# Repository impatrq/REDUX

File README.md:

<!-- README.md · Presentación del repo: qué es, hardware, compilar, uf2, cargar y uso. -->

# REDUX firmware

Firmware en C11 del **exoesqueleto de codo REDUX**, sobre Raspberry Pi Pico 2 W (RP2350)
y Pico SDK 2.x. Lee la actividad muscular de **bíceps y tríceps** por EMG, decide la
intención con una **lógica XOR**, y mueve el codo con un motor a través de un puente H
**BTS7960**. Un **encoder magnético AS5600** (I2C) mide el ángulo para respetar los
límites articulares. La seguridad es lo primero: co-contracción, límite alcanzado o falla
del encoder cortan el motor de inmediato.

El plan de desarrollo por fases está en [docs/PLAN.md](docs/PLAN.md); el detalle de
hardware en [docs/hardware.md](docs/hardware.md) y la máquina de estados de seguridad en
[docs/state_machine.md](docs/state_machine.md).

## Estructura del repo

```
src/        Firmware real (app → control / sensors / actuators → hal → SDK)
Pruebas/    Pruebas unitarias (PC) y programas de banco (placa) — ver Pruebas/README.md
tools/      Scripts: make_uf2_wsl.ps1, flash.sh, make_entregas.ps1
docs/       Plan, hardware y máquina de estados
```

## Hardware y pinout

Placa: Raspberry Pi Pico 2 W (RP2350). `src/hal/board.h` y [docs/hardware.md](docs/hardware.md)
son la única fuente de verdad del pinout.

| Señal | GPIO | Notas |
| --- | --- | --- |
| EMG bíceps | GP26 / ADC0 | Señal rectificada (onda completa), sin suavizar, 0–3 V |
| EMG tríceps | GP27 / ADC1 | Ídem |
| BTS7960 RPWM (flexión) | GP8 | PWM 20 kHz, vía 6N137 (no invierte) |
| BTS7960 LPWM (extensión) | GP9 | PWM 20 kHz, vía 6N137 (no invierte) |
| AS5600 SDA / SCL | GP4 / GP5 | I2C0 a 400 kHz, dirección 0x36 |
| LED de estado | GP2 | Solo desarrollo (lo reemplaza la pantalla) |
| Pulsador | GP3 | Solo desarrollo, pull-up interno, activo en bajo |

- **R_EN y L_EN del BTS7960 van fijos a +5 V** del lado del motor: el firmware no los
  maneja. El corte del motor es siempre **RPWM = LPWM = 0**.
- Dos masas aisladas (GND1 potencia / GND2 lógica); el único cruce son RPWM/LPWM por
  optoacopladores 6N137. Con la Pico apagada, los 6N137 dejan ambas señales en alto =
  **freno** (arranque seguro). Detalles en [docs/hardware.md](docs/hardware.md).

## Compilar el firmware

```sh
cmake -B build -G Ninja -DPICO_BOARD=pico2_w
cmake --build build
```

Esto compila el firmware (`redux-firmware`) y los programas de banco (`fase1_check`,
`fase2_check`, `fase3_check`, `emg_check`). Para compilar **solo el firmware**, sin los
bancos:

```sh
cmake -B build -G Ninja -DPICO_BOARD=pico2_w -DREDUX_BUILD_BANCOS=OFF
cmake --build build
```

### Generar el `.uf2` (picotool bloqueado por Device Guard)

En esta máquina, Device Guard / Smart App Control a veces bloquea `picotool.exe`, el paso
de empaquetado que CMake invoca al final: el `.elf` se enlaza bien (`build/redux-firmware.elf`),
pero el build corta sin producir el `.uf2`. Para generarlo se usa un `picotool` nativo de
Linux compilado en WSL 2:

```powershell
tools\make_uf2_wsl.ps1
```

La primera vez compila `picotool` dentro de WSL (en `~/.local/bin`, no en el repo), usando
como `PICO_SDK_PATH` el SDK ya instalado en Windows; después solo convierte. Para otro
ejecutable (por ejemplo un banco):

```powershell
tools\make_uf2_wsl.ps1 -Elf build\emg_check.elf -Uf2 build\emg_check.uf2
```

## Cargar en la Pico

Poner la Pico en modo BOOTSEL (mantener el botón al conectar) y copiar el `.uf2` a la
unidad `RPI-RP2`, o bien:

```sh
tools/flash.sh
```

## Pruebas

- **Unitarias (PC, Unity):** la forma oficial es por WSL —
  `powershell -ExecutionPolicy Bypass -File Pruebas\unitarias\run_tests_wsl.ps1`.
- **De banco (sobre la placa):** un programa por fase en `Pruebas/banco/`.

Todo el detalle en [Pruebas/README.md](Pruebas/README.md).

## Comandos serie del firmware

Por el monitor serie USB (una línea por comando):

| Comando | Efecto |
| --- | --- |
| `b N` | Intensidad simulada de bíceps (flexión) al N % (0–100) |
| `t N` | Intensidad simulada de tríceps (extensión) al N % |
| `r` | Reposo: ambos canales a 0 |
| `ok` | Confirmar (arranque / calibración) |
| `cancel` | Cancelar el paso actual |
| `recal` | Volver a calibrar desde el rango (ROM) |
| `hang` | Solo en modo banco: cuelga el lazo para probar el watchdog |

En el banco (sin electrodos) la fuente de EMG es **simulada por serie** (`b`/`t`/`r`); con
el paciente conectado se pasa a ADC (ver `EMG_SOURCE` en `src/common/config.h`). El
firmware emite un reporte de estado por USB periódicamente.

## Estados (supervisor de seguridad)

```
BOOT → CHECK_ENC → CALIB_ROM → CALIB_REST → CALIB_MVC → ARMING → RUN
                                                                    ↕
                                                                  FAULT
```

El motor **solo recibe PWM en `RUN`**. Cualquier falla (encoder, saturación de EMG,
sobrepaso del ciclo) lleva a `FAULT` con corte inmediato; el rearme exige lecturas
estables y ambos músculos en reposo. Transiciones completas en
[docs/state_machine.md](docs/state_machine.md).

## Abrir el proyecto en VS Code

La carpeta `.vscode/` **no se versiona** (es configuración local de cada máquina), así que
al clonar el repo no viene incluida. Dos formas de trabajar:

- **Extensión Raspberry Pi Pico:** instalar la extensión *Raspberry Pi Pico* en VS Code y
  usar *Pico: Import Project* sobre la carpeta del repo (board `pico2_w`, Pico SDK 2.x). La
  extensión regenera su propia configuración de `.vscode/` y los comandos de build/flash.
- **Por línea de comandos:** no hace falta VS Code. Alcanza con tener instalados el Pico
  SDK 2.x, CMake y Ninja, y usar los comandos de *Compilar el firmware* de arriba.

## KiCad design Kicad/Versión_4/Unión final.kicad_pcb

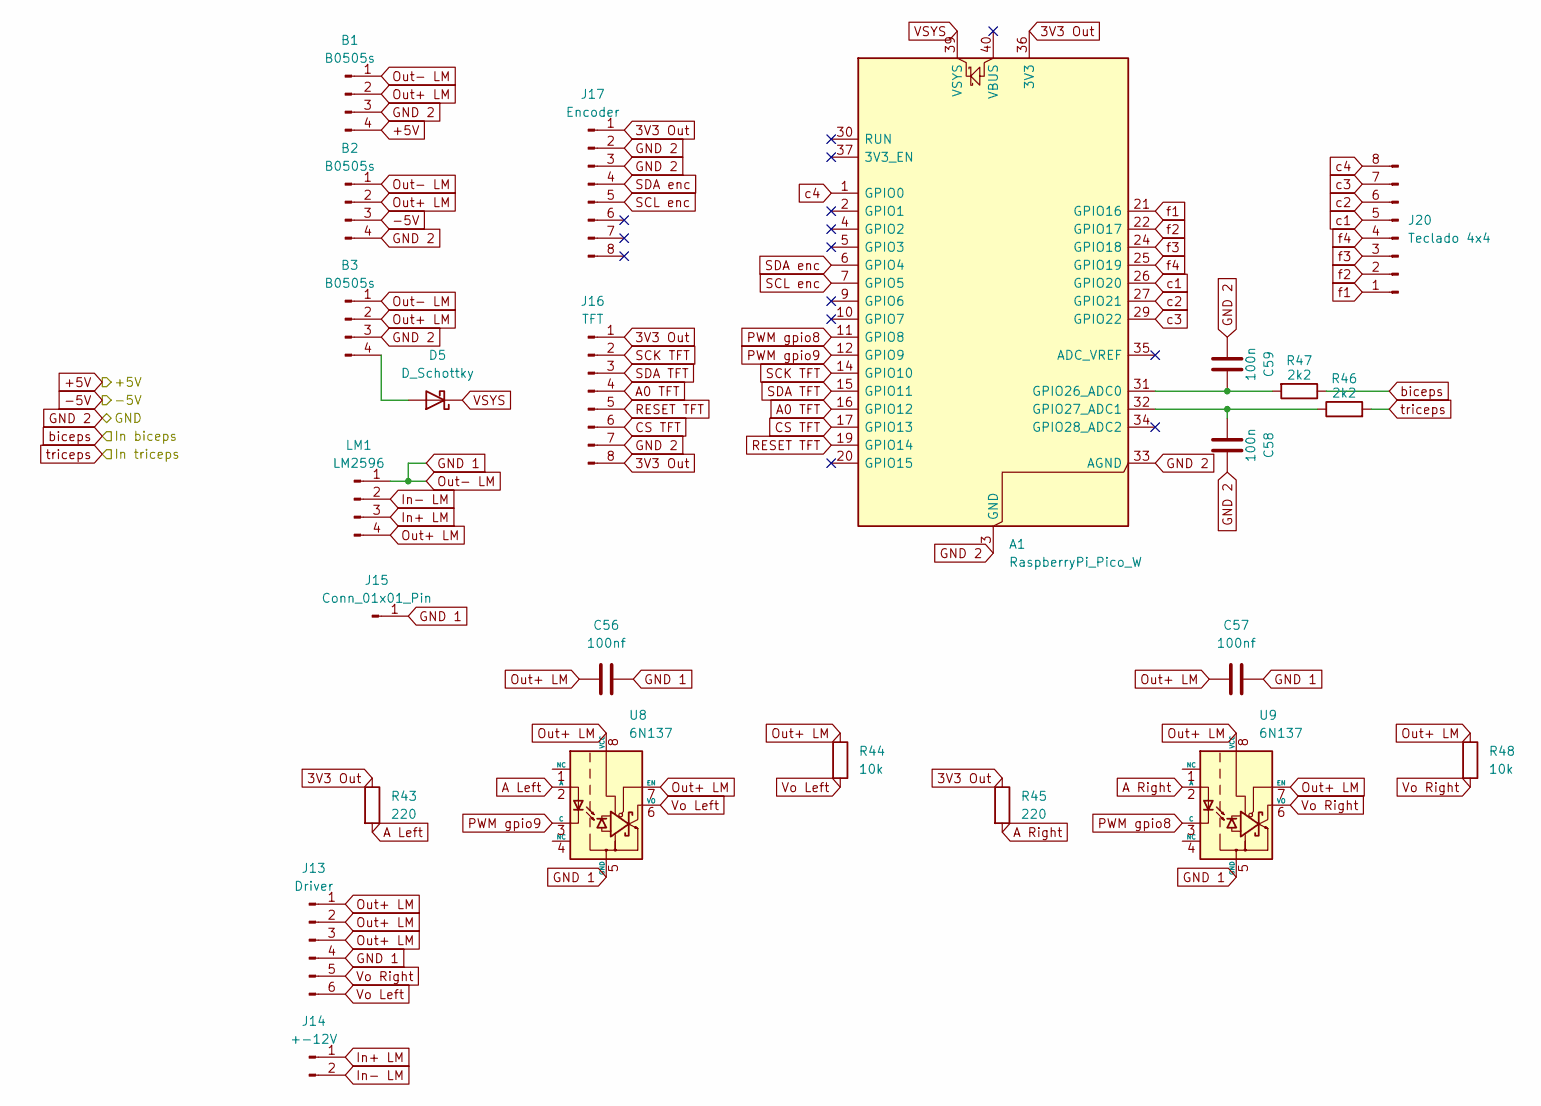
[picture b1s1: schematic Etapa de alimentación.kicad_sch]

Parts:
A1: RaspberryPi_Pico_W; RaspberryPi_Pico_Common_THT
B1, B2, B3: B0505s; B0505S-1w
C56, C57: 100nf; C_Disc_D10.0mm_W2.5mm_P5.00mm
C58, C59: 100n; C_0805_2012Metric_Pad1.18x1.45mm_HandSolder
D5: D_Schottky; D_DO-41_SOD81_P10.16mm_Horizontal
J13: Driver; PinHeader_1x06_P2.54mm_Vertical
J14: +-12V; TerminalBlock_MetzConnect_Type011_RT05502HBLC_1x02_P5.00mm_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
J15: Conn_01x01_Pin; PinHeader_1x01_P2.54mm_Vertical
J16: TFT; PinHeader_1x08_P2.54mm_Vertical
J17: Encoder; Molex_KK-254_AE-6410-08A_1x08_P2.54mm_Vertical
J20: Teclado 4x4; PinHeader_1x08_P2.54mm_Vertical
LM1: LM2596
R43, R45: 220; R_Axial_DIN0207_L6.3mm_D2.5mm_P10.16mm_Horizontal
R44, R48: 10k; R_Axial_DIN0207_L6.3mm_D2.5mm_P10.16mm_Horizontal
R46, R47: 2k2; R_Axial_DIN0207_L6.3mm_D2.5mm_P10.16mm_Horizontal
U8, U9: 6N137; DIP-8_W7.62mm

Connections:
3V3 Out: A1.36 (3V3), J16.1, J16.8, J17.1, R43.1, R45.1
+5V: B1.4; also elsewhere on the board
-5V: B2.3; also elsewhere on the board
A0 TFT: A1.16 (GPIO12), J16.4
A Left: R43.2, U8.2 (A)
A Right: R45.2, U9.2 (A)
CS TFT: A1.17 (GPIO13), J16.6
GND: A1.3 (GND), A1.8 (GND), A1.13 (GND), A1.18 (GND), A1.23 (GND), A1.28 (GND), A1.33 (AGND), A1.38 (GND), B1.3, B2.4, B3.3, C58.2, C59.1, J16.7, J17.2, J17.3; also elsewhere on the board
GND 1: B1.1, B2.1, B3.1, C56.2, C57.2, J13.4, J15.1 (Pin_1_1), LM1.1, U8.5 (GND), U9.5 (GND)
In+ LM: J14.1, LM1.3
In- LM: J14.2, LM1.2
unnamed: A1.31 (GPIO26_ADC0), C59.2, R47.2
unnamed: A1.32 (GPIO27_ADC1), C58.1, R46.1
unnamed: B3.4, D5.2 (A)
Out+ LM: B1.2, B2.2, B3.2, C56.1, C57.1, J13.1, J13.2, J13.3, LM1.4, R44.1, R48.1, U8.7 (EN), U8.8 (VCC), U9.7 (EN), U9.8 (VCC)
PWM gpio8: A1.11 (GPIO8), U9.3 (C)
PWM gpio9: A1.12 (GPIO9), U8.3 (C)
RESET TFT: A1.19 (GPIO14), J16.5
Rectificador biceps: R47.1; also elsewhere on the board
Rectificador triceps: R46.2; also elsewhere on the board
SCK TFT: A1.14 (GPIO10), J16.2
SCL enc: A1.7 (GPIO5), J17.5
SDA TFT: A1.15 (GPIO11), J16.3
SDA enc: A1.6 (GPIO4), J17.4
VSYS: A1.39 (VSYS), D5.1 (K)
Vo Left: J13.6, R44.2, U8.6 (VO)
Vo Right: J13.5, R48.2, U9.6 (VO)
c1: A1.26 (GPIO20), J20.5
c2: A1.27 (GPIO21), J20.6
c3: A1.29 (GPIO22), J20.7
c4: A1.1 (GPIO0), J20.8
f1: A1.21 (GPIO16), J20.1
f2: A1.22 (GPIO17), J20.2
f3: A1.24 (GPIO18), J20.3
f4: A1.25 (GPIO19), J20.4

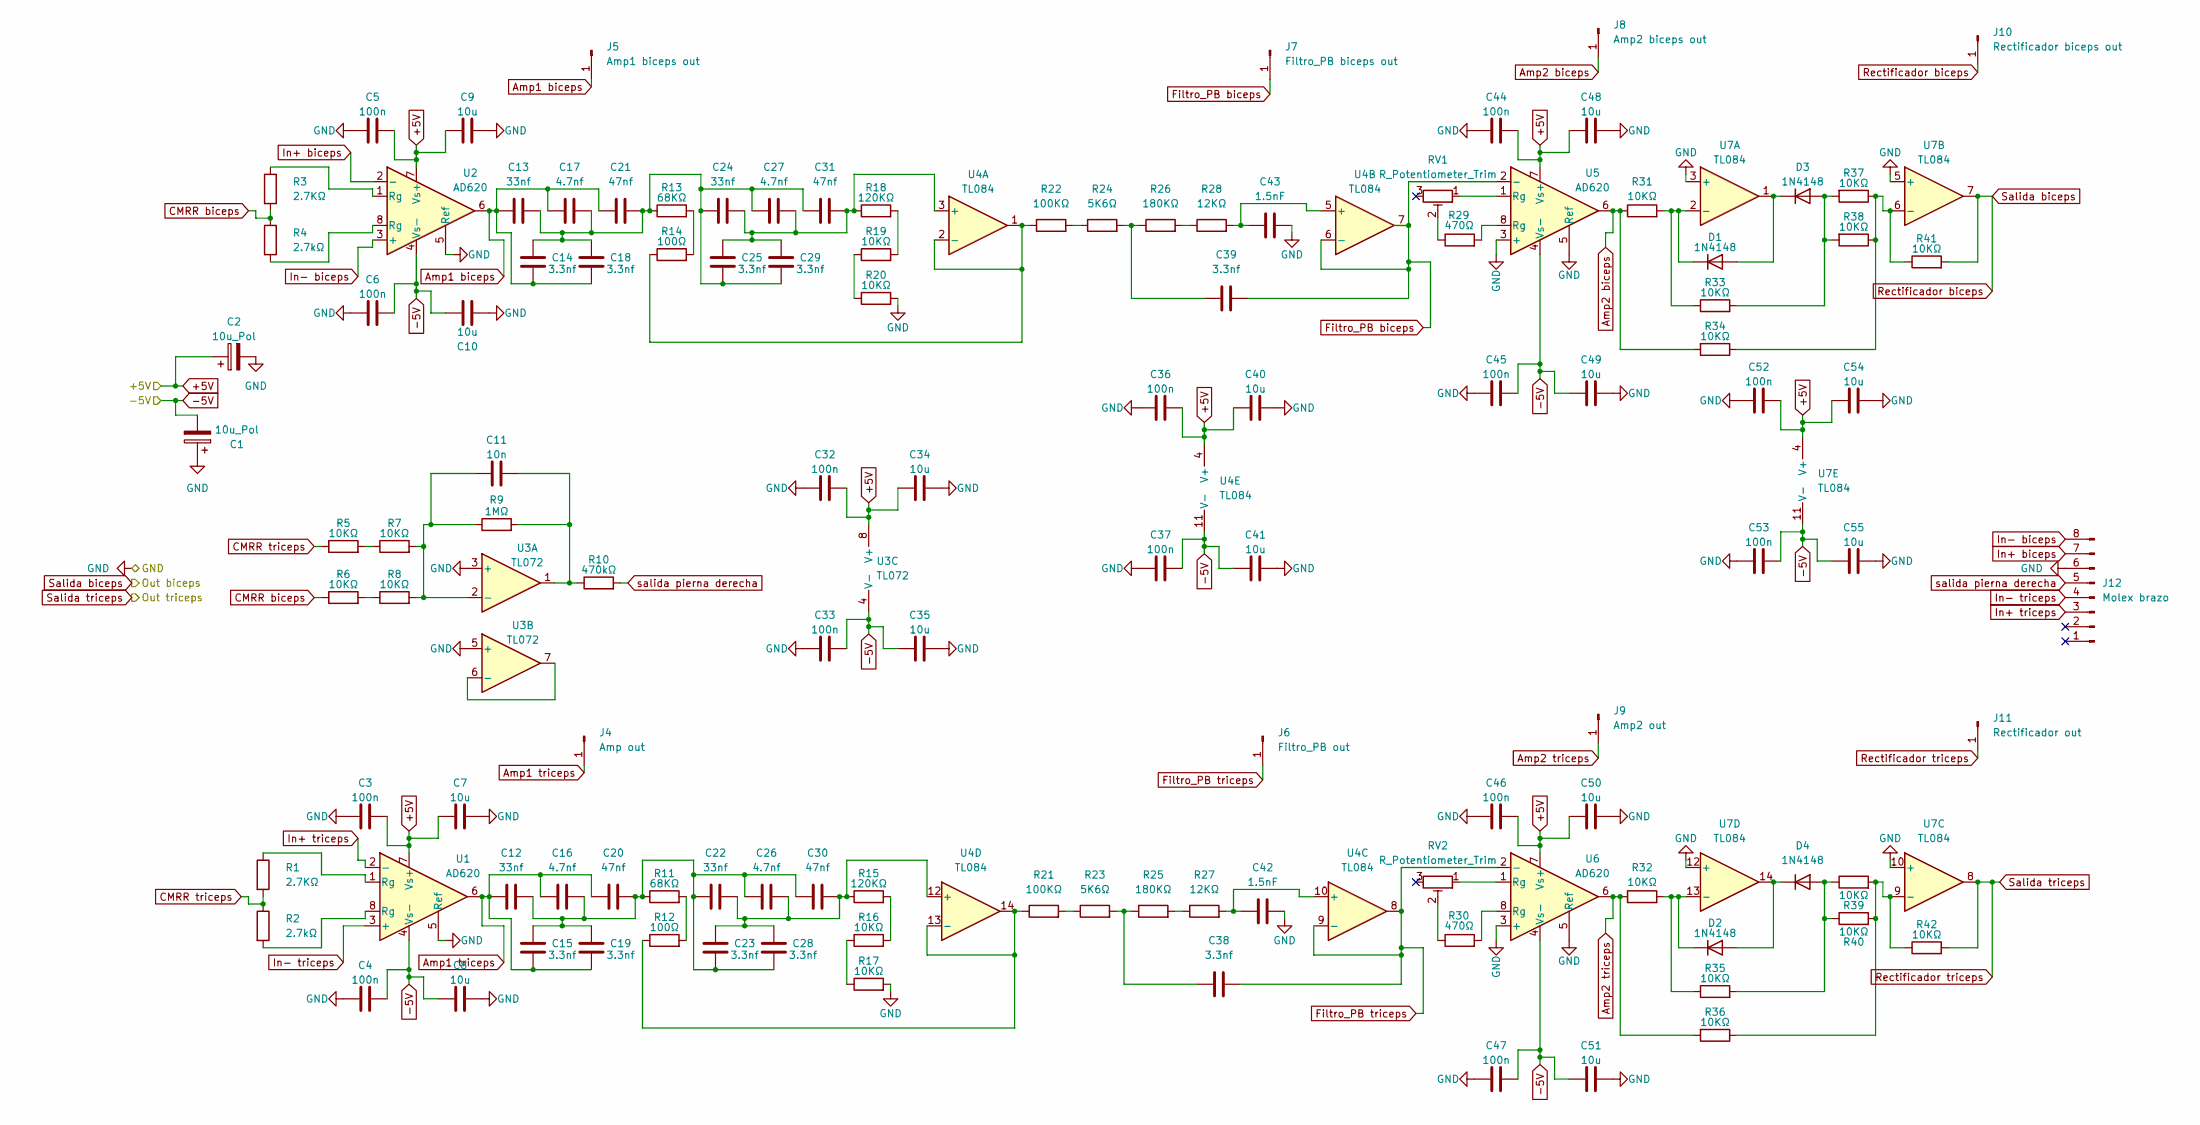
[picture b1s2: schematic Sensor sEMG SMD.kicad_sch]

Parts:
C1, C2: 10u_Pol; CP_Radial_D5.0mm_P2.00mm
C3, C4, C5, C6, C32, C33, C36, C37, C44, C45, C46, C47, C52, C53: 100n; C_0805_2012Metric_Pad1.18x1.45mm_HandSolder
C7, C8, C9, C10, C34, C35, C40, C41, C48, C49, C50, C51, C54, C55: 10u; C_0805_2012Metric_Pad1.18x1.45mm_HandSolder
C11: 10n; C_0805_2012Metric_Pad1.18x1.45mm_HandSolder
C12, C13, C22, C24: 33nf; C_0805_2012Metric_Pad1.18x1.45mm_HandSolder
C14, C15, C18, C19, C23, C25, C28, C29, C38, C39: 3.3nf; C_0805_2012Metric_Pad1.18x1.45mm_HandSolder
C16, C17, C26, C27: 4.7nf; C_0805_2012Metric_Pad1.18x1.45mm_HandSolder
C20, C21, C30, C31: 47nf; C_0805_2012Metric_Pad1.18x1.45mm_HandSolder
C42, C43: 1.5nF; C_0805_2012Metric_Pad1.18x1.45mm_HandSolder
D1, D2, D3, D4: 1N4148; D_SOD-123
J4: Amp out; PinHeader_1x01_P2.00mm_Vertical
J5: Amp1 biceps out; PinHeader_1x01_P2.00mm_Vertical
J6: Filtro_PB out; PinHeader_1x01_P2.00mm_Vertical
J7: Filtro_PB biceps out; PinHeader_1x01_P2.00mm_Vertical
J8: Amp2 biceps out; PinHeader_1x01_P2.00mm_Vertical
J9: Amp2 out; PinHeader_1x01_P2.00mm_Vertical
J10: Rectificador biceps out; PinHeader_1x01_P2.00mm_Vertical
J11: Rectificador out; PinHeader_1x01_P2.00mm_Vertical
J12: Molex brazo; Molex_KK-254_AE-6410-08A_1x08_P2.54mm_Vertical
R1, R3: 2.7KΩ; R_0805_2012Metric_Pad1.20x1.40mm_HandSolder
R2, R4: 2.7kΩ; R_0805_2012Metric_Pad1.20x1.40mm_HandSolder
R5, R6, R7, R8, R16, R17, R19, R20, R31, R32, R33, R34, R35, R36, R37, R38, R39, R40, R41, R42: 10KΩ; R_0805_2012Metric_Pad1.20x1.40mm_HandSolder
R9: 1MΩ; R_0805_2012Metric_Pad1.20x1.40mm_HandSolder
R10: 470kΩ; R_0805_2012Metric_Pad1.20x1.40mm_HandSolder
R11, R13: 68KΩ; R_0805_2012Metric_Pad1.20x1.40mm_HandSolder
R12, R14: 100Ω; R_0805_2012Metric_Pad1.20x1.40mm_HandSolder
R15, R18: 120KΩ; R_0805_2012Metric_Pad1.20x1.40mm_HandSolder
R21, R22: 100KΩ; R_0805_2012Metric_Pad1.20x1.40mm_HandSolder
R23, R24: 5K6Ω; R_0805_2012Metric_Pad1.20x1.40mm_HandSolder
R25, R26: 180KΩ; R_0805_2012Metric_Pad1.20x1.40mm_HandSolder
R27, R28: 12KΩ; R_0805_2012Metric_Pad1.20x1.40mm_HandSolder
R29, R30: 470Ω; R_0805_2012Metric_Pad1.20x1.40mm_HandSolder
RV1, RV2: R_Potentiometer_Trim; Potentiometer_Bourns_3296W_Vertical
U1, U2, U5, U6: AD620; SOIC-8_3.9x4.9mm_P1.27mm
U3: TL072; SOIC-8_3.9x4.9mm_P1.27mm
U4, U7: TL084; SOIC-14_3.9x8.7mm_P1.27mm

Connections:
+5V: C2.1, C3.2, C5.2, C7.1, C9.1, C32.2, C34.1, C36.2, C40.1, C44.2, C46.2, C48.1, C50.1, C52.2, C54.1, U1.7 (Vs+), U2.7 (Vs+), U3.8 (V+), U4.4 (V+), U5.7 (Vs+), U6.7 (Vs+), U7.4 (V+); also elsewhere on the board
-5V: C1.2, C4.2, C6.2, C8.1, C10.2, C33.2, C35.1, C37.2, C41.1, C45.2, C47.2, C49.1, C51.1, C53.2, C55.1, U1.4 (Vs-), U2.4 (Vs-), U3.4 (V-), U4.11 (V-), U5.4 (Vs-), U6.4 (Vs-), U7.11 (V-); also elsewhere on the board
Amp1 biceps: C13.1, C14.2, C17.1, C18.2, C21.1, J5.1 (Pin_1_1), U2.6
Amp1 triceps: C12.1, C15.2, C16.1, C19.2, C20.1, J4.1 (Pin_1_1), U1.6
Amp2 biceps: J8.1 (Pin_1_1), R31.1, R34.2, U5.6
Amp2 triceps: J9.1 (Pin_1_1), R32.1, R36.2, U6.6
CMRR biceps: R3.2, R4.1, R6.1
CMRR triceps: R1.2, R2.1, R5.1
Filtro_PB biceps: C39.2, J7.1 (Pin_1_1), U4.6 (-), U4.7, U5.2 (-)
Filtro_PB triceps: C38.2, J6.1 (Pin_1_1), U4.8, U4.9 (-), U6.2 (-)
GND: C1.1, C2.2, C3.1, C4.1, C5.1, C6.1, C7.2, C8.2, C9.2, C10.1, C32.1, C33.1, C34.2, C35.2, C36.1, C37.1, C40.2, C41.2, C42.2, C43.2, C44.1, C45.1, C46.1, C47.1, C48.2, C49.2, C50.2, C51.2, C52.1, C53.1, C54.2, C55.2, J12.6, R17.2, R20.2, U1.5 (Ref), U2.5 (Ref), U3.3 (+), U3.5 (+), U5.3 (+), U5.5 (Ref), U6.3 (+), U6.5 (Ref), U7.3 (+), U7.5 (+), U7.10 (+), U7.12 (+); also elsewhere on the board
In+ biceps: J12.7, U2.2 (-)
In+ triceps: J12.3, U1.2 (-)
In- biceps: J12.8, U2.3 (+)
In- triceps: J12.4, U1.3 (+)
unnamed: C11.2, R9.2, R10.1, U3.1
unnamed: C12.2, C15.1, C16.2, C19.1, C20.2, C22.1, C23.2, C26.1, C28.2, C30.1, R11.1
unnamed: C13.2, C14.1, C17.2, C18.1, C21.2, C24.1, C25.2, C27.1, C29.2, C31.1, R13.1
unnamed: C38.1, R23.2, R25.1
unnamed: C39.1, R24.2, R26.1
unnamed: D1.2 (A), D3.1 (K), U7.1
unnamed: D1.1 (K), R31.2, R33.1, U7.2 (-)
unnamed: D2.2 (A), D4.1 (K), U7.14
unnamed: D2.1 (K), R32.2, R35.1, U7.13 (-)
unnamed: D3.2 (A), R33.2, R37.2, R38.2
unnamed: D4.2 (A), R35.2, R39.1, R40.1
unnamed: R1.1, U1.1 (Rg)
unnamed: R2.2, U1.8 (Rg)
unnamed: R3.1, U2.1 (Rg)
unnamed: R4.2, U2.8 (Rg)
unnamed: R5.2, R7.1
unnamed: R6.2, R8.1
unnamed: R11.2, R12.2
unnamed: R13.2, R14.2
unnamed: R15.2, R16.2
unnamed: R16.1, R17.1
unnamed: R18.2, R19.2
unnamed: R19.1, R20.1
unnamed: R21.2, R23.1
unnamed: R22.2, R24.1
unnamed: R25.2, R27.1
unnamed: R26.2, R28.1
unnamed: R29.1, RV1.2
unnamed: R29.2, U5.8 (Rg)
unnamed: R30.1, RV2.2
unnamed: R30.2, U6.8 (Rg)
unnamed: RV1.1, U5.1 (Rg)
unnamed: RV2.1, U6.1 (Rg)
unnamed: C11.1, R7.2, R8.2, R9.1, U3.2 (-)
unnamed: U3.6 (-), U3.7
unnamed: C24.2, C25.1, C27.2, C29.1, C31.2, R18.1, U4.3 (+)
unnamed: R14.1, R22.1, U4.1, U4.2 (-)
unnamed: C43.1, R28.2, U4.5 (+)
unnamed: C42.1, R27.2, U4.10 (+)
unnamed: C22.2, C23.1, C26.2, C28.1, C30.2, R15.1, U4.12 (+)
unnamed: R12.1, R21.1, U4.13 (-), U4.14
unnamed: R34.1, R37.1, R38.1, R41.1, U7.6 (-)
unnamed: R36.1, R39.2, R40.2, R42.1, U7.9 (-)
Rectificador biceps: J10.1 (Pin_1_1), R41.2, U7.7; also elsewhere on the board
Rectificador triceps: J11.1 (Pin_1_1), R42.2, U7.8; also elsewhere on the board
salida pierna derecha: J12.5, R10.2

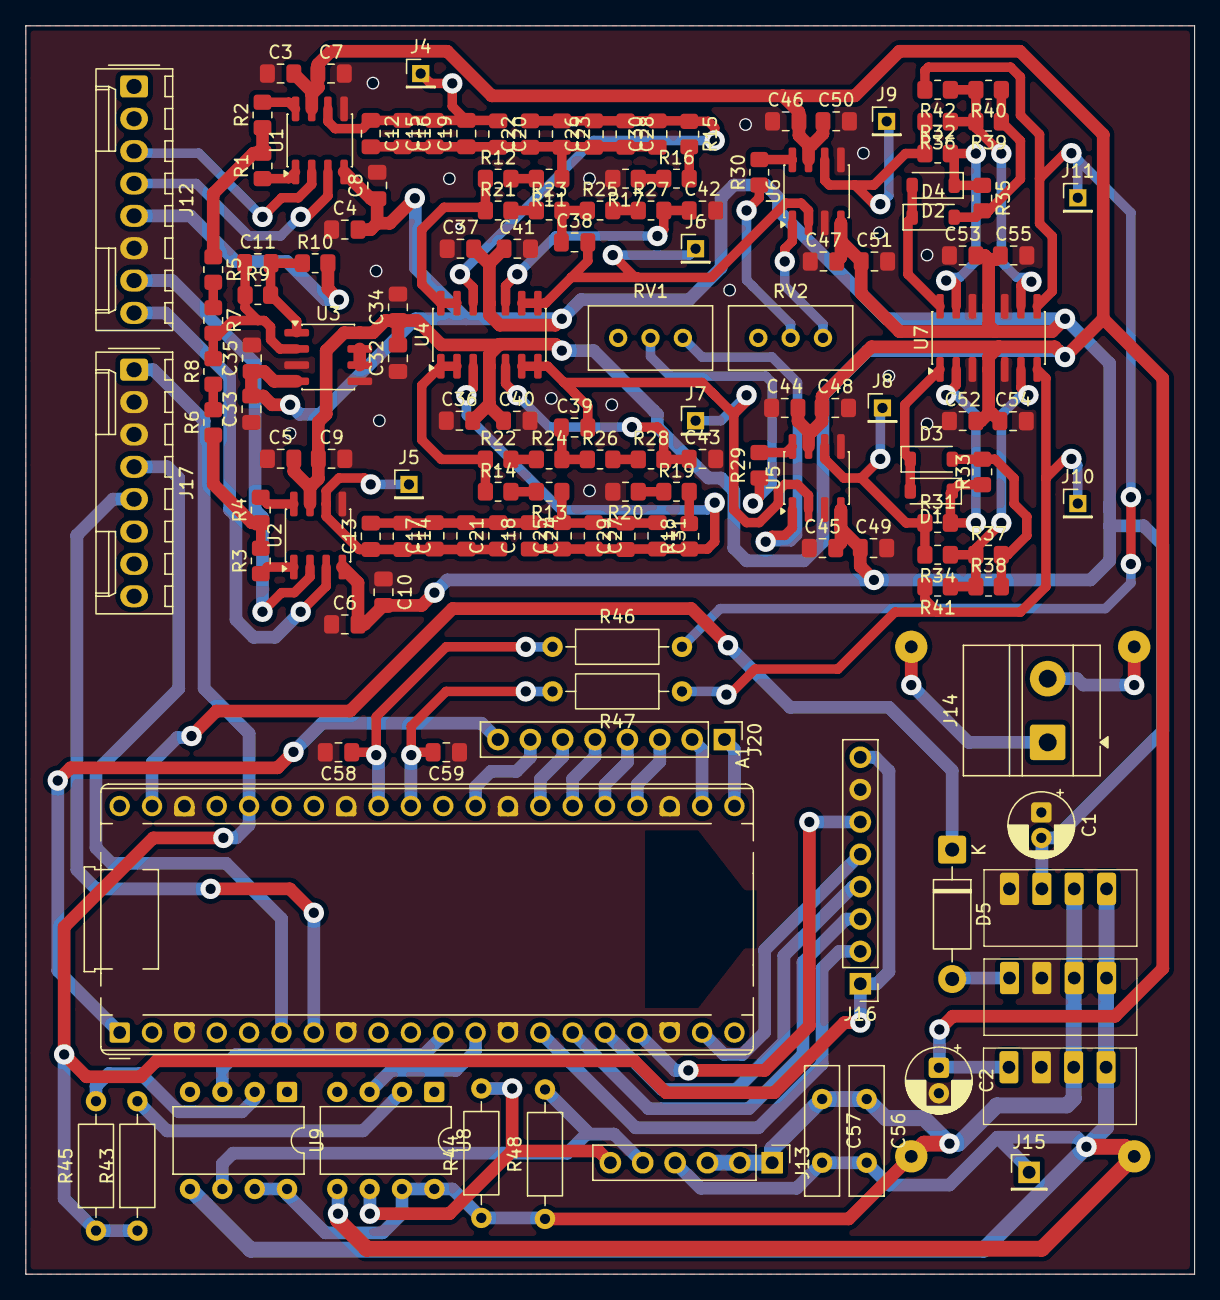
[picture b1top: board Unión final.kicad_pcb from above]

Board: 2 copper layers, 91.8 x 98.0 mm, 143 parts (1 on the bottom side), 91 nets.

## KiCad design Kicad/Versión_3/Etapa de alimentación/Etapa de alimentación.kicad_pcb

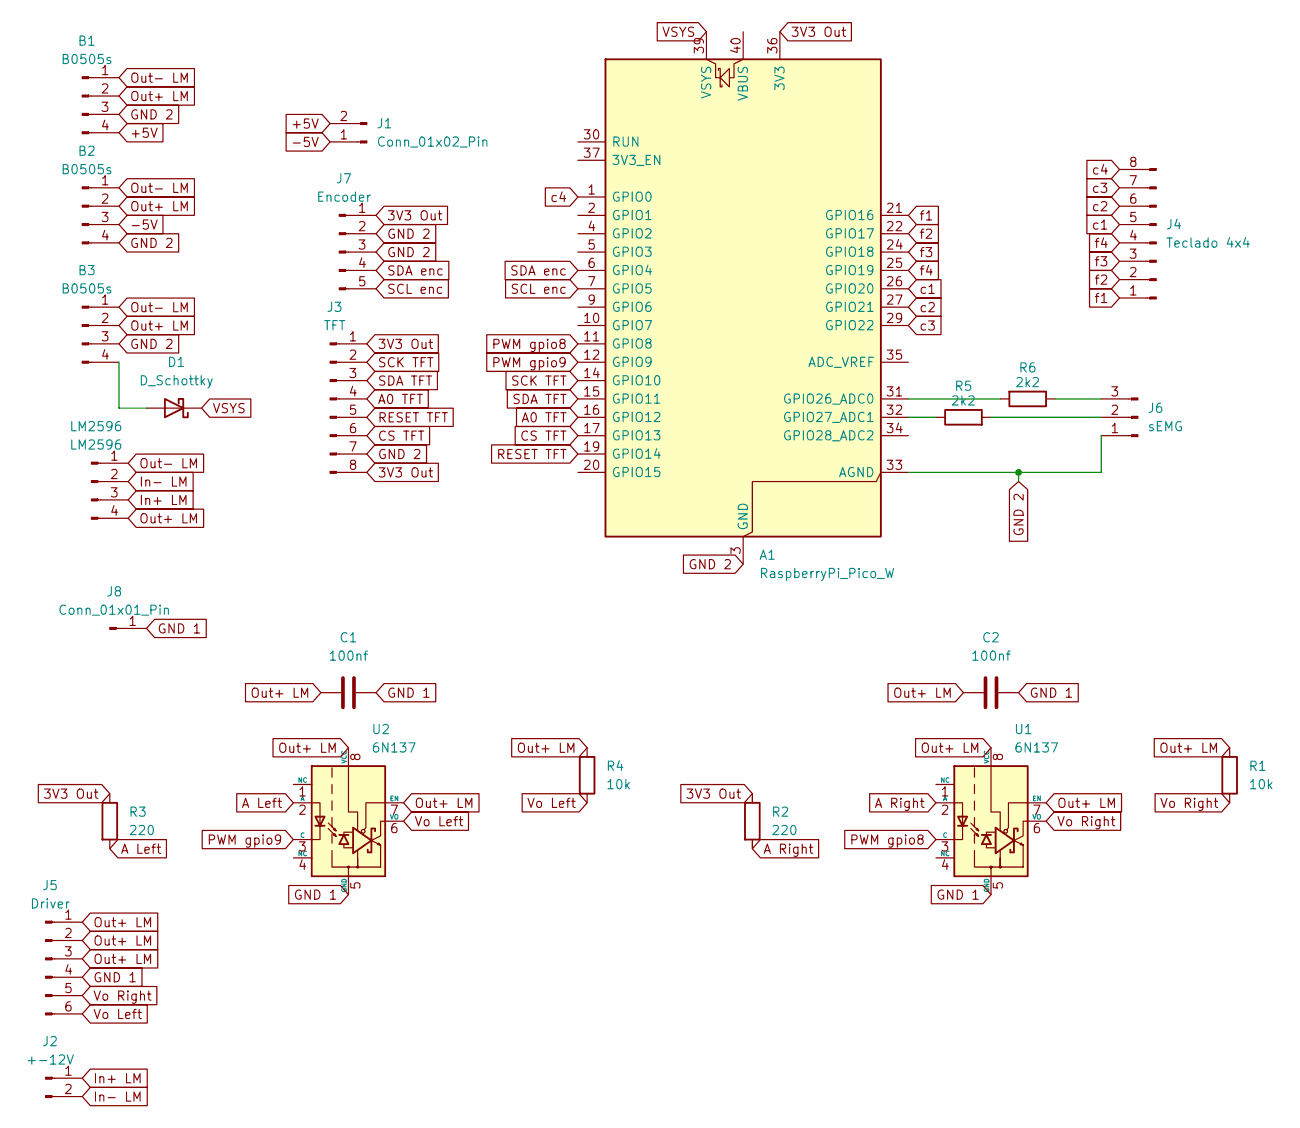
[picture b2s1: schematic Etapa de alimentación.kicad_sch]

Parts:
A1: RaspberryPi_Pico_W; RaspberryPi_Pico_Common_THT
B1, B2, B3: B0505s; B0505S-1w
C1, C2: 100nf; C_Disc_D10.0mm_W2.5mm_P5.00mm
D1: D_Schottky; D_5W_P12.70mm_Horizontal
J1: Conn_01x02_Pin; TerminalBlock_MetzConnect_Type011_RT05502HBLC_1x02_P5.00mm_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
J2: +-12V; TerminalBlock_MetzConnect_Type011_RT05502HBLC_1x02_P5.00mm_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
J3: TFT; PinHeader_1x08_P2.54mm_Vertical
J4: Teclado 4x4; PinHeader_1x08_P2.54mm_Vertical
J5: Driver; PinHeader_1x06_P2.54mm_Vertical
J6: sEMG; TerminalBlock_MetzConnect_Type011_RT05503HBLC_1x03_P5.00mm_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
J7: Encoder; TerminalBlock_MetzConnect_Type011_RT05505HBLC_1x05_P5.00mm_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
J8: Conn_01x01_Pin; PinHeader_1x01_P2.54mm_Vertical
LM2596: LM2596
R1, R4: 10k; R_Axial_DIN0207_L6.3mm_D2.5mm_P10.16mm_Horizontal
R2, R3: 220; R_Axial_DIN0207_L6.3mm_D2.5mm_P10.16mm_Horizontal
R5, R6: 2k2; R_Axial_DIN0207_L6.3mm_D2.5mm_P10.16mm_Horizontal
U1, U2: 6N137; DIP-8_W7.62mm

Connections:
3V3 Out: A1.36 (3V3), J3.1, J3.8, J7.1, R2.1, R3.1
+5V: B1.4, J1.2
-5V: B2.3, J1.1
A0 TFT: A1.16 (GPIO12), J3.4
A Left: R3.2, U2.2 (A)
A Right: R2.2, U1.2 (A)
CS TFT: A1.17 (GPIO13), J3.6
GND 1: C1.2, C2.2, J5.4, J8.1 (Pin_1_1), U1.5 (GND), U2.5 (GND)
GND 2: A1.3 (GND), A1.8 (GND), A1.13 (GND), A1.18 (GND), A1.23 (GND), A1.28 (GND), A1.33 (AGND), A1.38 (GND), B1.3, B2.4, B3.3, J3.7, J6.1, J7.2, J7.3
In+ LM: J2.1, LM2596.3
In- LM: J2.2, LM2596.2
unnamed: A1.31 (GPIO26_ADC0), R6.2
unnamed: A1.32 (GPIO27_ADC1), R5.1
unnamed: B3.4, D1.2 (A)
unnamed: J6.2, R5.2
unnamed: J6.3, R6.1
Out+ LM: B1.2, B2.2, B3.2, C1.1, C2.1, J5.1, J5.2, J5.3, LM2596.4, R1.1, R4.1, U1.7 (EN), U1.8 (VCC), U2.7 (EN), U2.8 (VCC)
Out- LM: B1.1, B2.1, B3.1, LM2596.1
PWM gpio8: A1.11 (GPIO8), U1.3 (C)
PWM gpio9: A1.12 (GPIO9), U2.3 (C)
RESET TFT: A1.19 (GPIO14), J3.5
SCK TFT: A1.14 (GPIO10), J3.2
SCL enc: A1.7 (GPIO5), J7.5
SDA TFT: A1.15 (GPIO11), J3.3
SDA enc: A1.6 (GPIO4), J7.4
VSYS: A1.39 (VSYS), D1.1 (K)
Vo Left: J5.6, R4.2, U2.6 (VO)
Vo Right: J5.5, R1.2, U1.6 (VO)
c1: A1.26 (GPIO20), J4.5
c2: A1.27 (GPIO21), J4.6
c3: A1.29 (GPIO22), J4.7
c4: A1.1 (GPIO0), J4.8
f1: A1.21 (GPIO16), J4.1
f2: A1.22 (GPIO17), J4.2
f3: A1.24 (GPIO18), J4.3
f4: A1.25 (GPIO19), J4.4

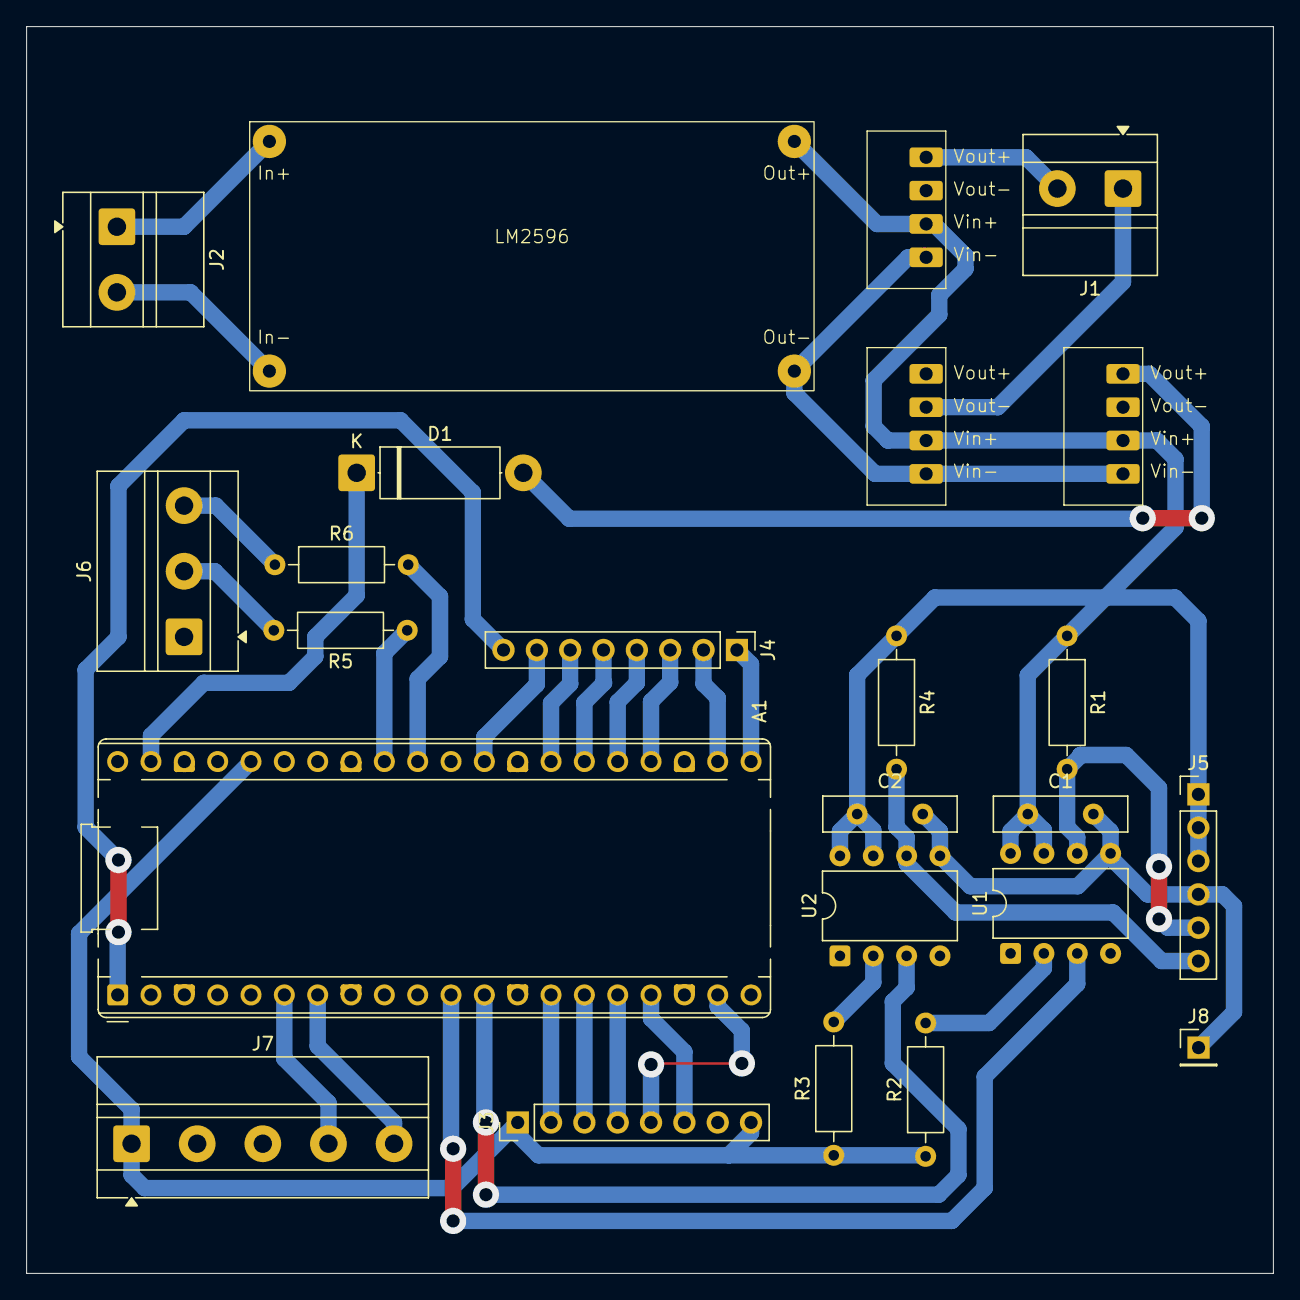
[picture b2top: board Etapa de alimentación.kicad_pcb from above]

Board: 2 copper layers, 95.0 x 95.0 mm, 24 parts (0 on the bottom side), 36 nets.

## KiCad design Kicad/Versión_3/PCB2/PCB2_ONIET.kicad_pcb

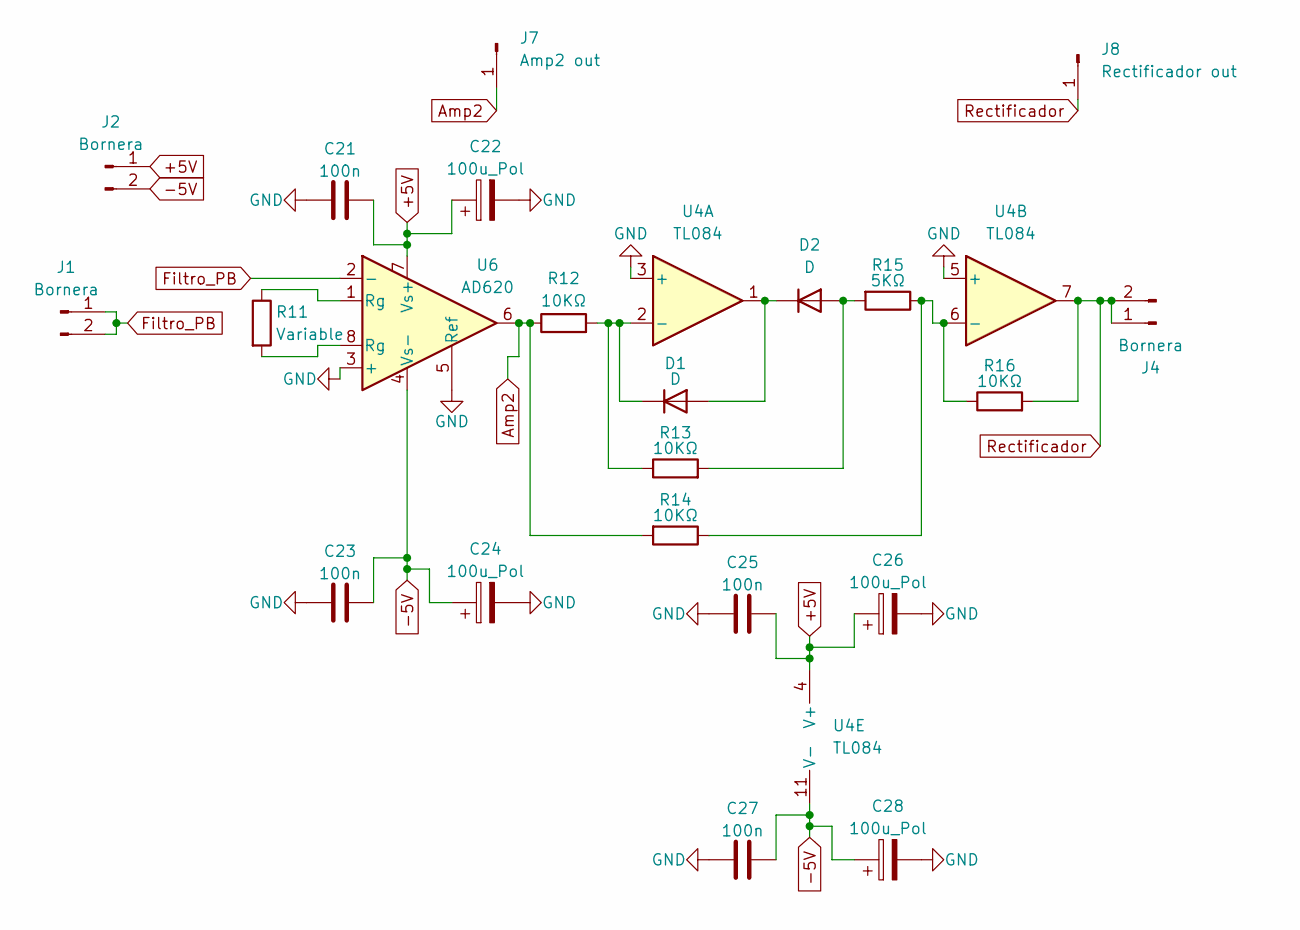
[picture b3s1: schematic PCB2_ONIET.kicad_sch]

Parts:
C21, C23, C25, C27: 100n; C_Disc_D10.5mm_W5.0mm_P10.00mm
C22, C24, C26, C28: 100u_Pol; C_Radial_D5.0mm_H11.0mm_P2.00mm
D1, D2: D; D_5W_P12.70mm_Horizontal
J1, J2, J4: Bornera; TerminalBlock_MetzConnect_Type011_RT05502HBLC_1x02_P5.00mm_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
J7: Amp2 out; PinHeader_1x01_P2.00mm_Vertical
J8: Rectificador out; PinHeader_1x01_P2.00mm_Vertical
R11: Variable; R_Axial_DIN0207_L6.3mm_D2.5mm_P10.16mm_Horizontal
R12, R13, R14, R16: 10KΩ; R_Axial_DIN0207_L6.3mm_D2.5mm_P10.16mm_Horizontal
R15: 5KΩ; R_Axial_DIN0207_L6.3mm_D2.5mm_P10.16mm_Horizontal
U4: TL084; DIP-14_W7.62mm_LongPads
U6: AD620; DIP-8_W7.62mm

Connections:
+5V: C21.2, C22.1, C25.2, C26.1, J2.1, U4.4 (V+), U6.7 (Vs+)
-5V: C23.2, C24.1, C27.2, C28.1, J2.2, U4.11 (V-), U6.4 (Vs-)
Amp2: J7.1 (Pin_1_1), R12.1, R14.2, U6.6
Filtro_PB: J1.1, J1.2, U6.2 (-)
GND: C21.1, C22.2, C23.1, C24.2, C25.1, C26.2, C27.1, C28.2, U4.3 (+), U4.5 (+), U6.3 (+), U6.5 (Ref)
unnamed: D1.2 (A), D2.1 (K), U4.1
unnamed: D1.1 (K), R12.2, R13.1, U4.2 (-)
unnamed: D2.2 (A), R13.2, R15.2
unnamed: R11.1, U6.1 (Rg)
unnamed: R11.2, U6.8 (Rg)
unnamed: R14.1, R15.1, R16.1, U4.6 (-)
Rectificador: J4.1, J4.2, J8.1 (Pin_1_1), R16.2, U4.7

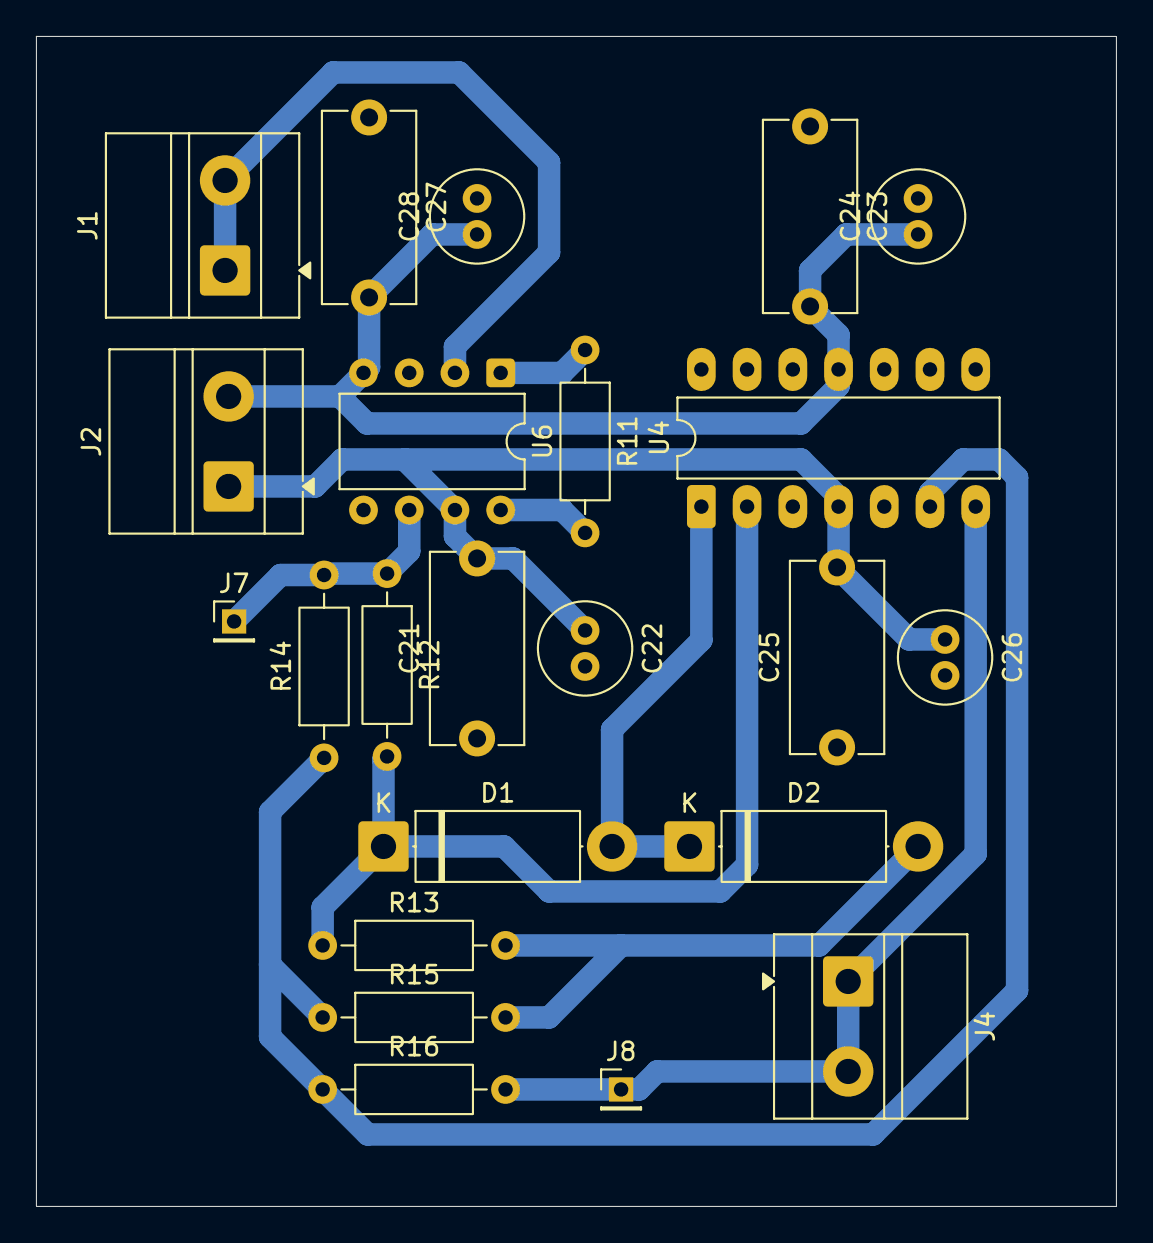
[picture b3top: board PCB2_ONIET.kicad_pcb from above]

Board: 2 copper layers, 60.0 x 65.0 mm, 23 parts (0 on the bottom side), 12 nets.
